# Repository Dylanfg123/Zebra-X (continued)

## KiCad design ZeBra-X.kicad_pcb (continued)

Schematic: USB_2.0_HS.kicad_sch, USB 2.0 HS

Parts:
C900, C901, C902, C903, C904: 100n; C_0402_1005Metric; Manufacturer PN CC0402KRX5R8BB104; LCSC PN C106256
C905, C906, C907, C908: 4u7; C_0402_1005Metric; Manufacturer PN CL05A475MP5NRNC; LCSC PN C23733
D900, D901, D902: CG0402MLU-3.3G; D_0402_1005Metric; Manufacturer PN CG0402MLU-3.3G; LCSC PN C2655393
D903: PMEG1030EJ,115; D_SOD-323F; Manufacturer PN PMEG1030EJ,115; LCSC PN C133633
FB900: 120R; L_0402_1005Metric; Manufacturer PN BLM15PX121SN1D; LCSC PN C88970
J900: GMSB0522132EU; Manufacturer PN GMSB0522132EU
R900: 1K; R_0402_1005Metric; Manufacturer PN RC0402FR-071KL; LCSC PN C106235
R901: 22R; R_0402_1005Metric; Manufacturer PN RC0402FR-0722RL; LCSC PN C114765
R902: 8K06; R_0402_1005Metric; Manufacturer PN RC0402FR-078K06L; LCSC PN C276278
R903: 12K; R_0402_1005Metric; Manufacturer PN RTT021202FTH; LCSC PN C102781
R904: 4K7; R_0402_1005Metric; Manufacturer PN RC0402FR-074K7L; LCSC PN C105871
U900: USB3320C-EZK; QFN32_5X5MC_MCH; Manufacturer PN USB3320C-EZK; LCSC PN C52447
U901: TPS2051CDBV; SOT-23-5; Manufacturer PN TPS2051CDBVR; LCSC PN C129581
X900: ECS-2520MV-130-BN-TR; Oscillator_SMD_ECS_2520MV-xxx-xx-4Pin_2.5x2.0mm; Manufacturer PN ECS-2520MV-130-BN-TR

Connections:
+1V8: C900.1, C902.1, C903.1, C904.1, R900.2, U900.14 (REFSEL2), U900.28 (VDD18), U900.30 (VDD18), U900.32 (VDDIO), X900.1 (EN), X900.4 (VDD); also elsewhere on the board
+3V3: C901.1, U900.20 (VDD33), U900.21 (VBAT); also elsewhere on the board
+5V: C907.1, U901.5 (IN); also elsewhere on the board
+5V_USB_SW: C908.1, D903.2 (A), U901.1 (OUT)
/[9] USB 2.0 HS/CLK_13MHZ: R901.1, X900.3 (OUT)
/[9] USB 2.0 HS/USB_HS_D_N: D900.1 (K), J900.2 (D-), U900.19 (DM)
/[9] USB 2.0 HS/USB_HS_D_P: D901.1 (K), J900.3 (D+), U900.18 (DP)
/[9] USB 2.0 HS/USB_HS_ID: D902.1 (K), J900.4 (ID), U900.23 (ID)
/[9] USB 2.0 HS/USB_HS_VBUS_FILT: C905.1, D903.1 (K), FB900.1, R903.2
/[9] USB 2.0 HS/USB_PHY_CPEN: R904.1, U900.17 (CPEN), U901.4 (EN)
/[9] USB 2.0 HS/USB_PHY_RBIAS: R902.1, U900.24 (RBIAS)
/[9] USB 2.0 HS/USB_PHY_VBUS: R903.1, U900.22 (VBUS)
/[9] USB 2.0 HS/USB_REFCLK_13MHZ: R901.2, U900.26 (REFCLK)
GND: C900.2, C901.2, C902.2, C903.2, C904.2, C905.2, C906.2, C907.2, C908.2, D900.2 (A), D901.2 (A), D902.2 (A), J900.5 (GND), R902.2, R904.2, U900.8 (REFSEL0), U900.11 (REFSEL1), U900.33 (GND), U901.2 (GND), X900.2 (GND); also elsewhere on the board
GNDPWR: J900.SH; also elsewhere on the board
unnamed: C906.1, FB900.2, J900.1 (VBUS)
USB_CLK: U900.1 (CLKOUT); also elsewhere on the board
USB_DATA0: U900.3 (DATA0); also elsewhere on the board
USB_DATA1: U900.4 (DATA1); also elsewhere on the board
USB_DATA2: U900.5 (DATA2); also elsewhere on the board
USB_DATA3: U900.6 (DATA3); also elsewhere on the board
USB_DATA4: U900.7 (DATA4); also elsewhere on the board
USB_DATA5: U900.9 (DATA5); also elsewhere on the board
USB_DATA6: U900.10 (DATA6); also elsewhere on the board
USB_DATA7: U900.13 (DATA7); also elsewhere on the board
USB_DIR: U900.31 (DIR); also elsewhere on the board
USB_NRST: R900.1, U900.27 (RESETB); also elsewhere on the board
USB_NXT: U900.2 (NXT); also elsewhere on the board
USB_STP: U900.29 (STP); also elsewhere on the board

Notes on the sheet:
USB PHY Reference Clock (13MHz)
ULPI
[9] USB 2.0 High-Speed (OTG)
REFSEL[2:0]=100 -> REFCLK=13MHz
USB HS PHY & Mini AB Connector

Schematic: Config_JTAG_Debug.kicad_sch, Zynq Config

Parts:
C300, C304, C306, C307, C308, C309, C310, C311, C312, C313, C314, C316, C318: 100n; C_0402_1005Metric; Manufacturer PN CC0402KRX5R8BB104; LCSC PN C106256
C301, C302, C303, C305, C315: 4u7; C_0402_1005Metric; Manufacturer PN CL05A475MP5NRNC; LCSC PN C23733
D300, D308, D309: LED_GREEN; LED_0402_1005Metric; Manufacturer PN SZYY0402YG; LCSC PN C434449
D301, D302, D303, D304, D306, D307: CG0402MLU-3.3G; D_0402_1005Metric; Manufacturer PN CG0402MLU-3.3G; LCSC PN C2655393
D305: PMEG1030EJ,115; D_SOD-323F; Manufacturer PN PMEG1030EJ,115; LCSC PN C133633
FB300, FB301, FB302: 120R; L_0402_1005Metric; Manufacturer PN BLM15PX121SN1D; LCSC PN C88970
J300: DigilentH2SHeader; PinHeader_1x06_P2.54mm_Vertical
J301: USB3100-30-A; CONN_USB3100-30-A_GCT; Manufacturer PN USB3100-30-A
Q300: T2N7002AK,LM; SOT23_TOS; Manufacturer PN T2N7002AK,LM; LCSC PN C516175
R300, R301, R302, R303, R304: 4K7; R_0402_1005Metric; Manufacturer PN RC0402FR-074K7L; LCSC PN C105871
R305, R306, R307, R308, R329, R330, R331, R332, R333, R334, R335, R338: 22R; R_0402_1005Metric; Manufacturer PN RC0402FR-0722RL; LCSC PN C114765
R309, R336, R337: 510R; R_0402_1005Metric; Manufacturer PN RC0402FR-07510RL; LCSC PN C276273
R310, R312, R314, R316, R319: 20K; R_0402_1005Metric; Manufacturer PN RC0402FR-0720KL; LCSC PN C93942
R311, R313, R315, R318, R321: 1K; R_0402_1005Metric; Manufacturer PN RC0402FR-071KL; LCSC PN C106235
R317, R320: DNP_0R; R_0402_1005Metric; not fitted
R322, R323: 100K; R_0402_1005Metric; Manufacturer PN RC0402FR-07100KL; LCSC PN C60491
R324, R326, R327, R328: 12K; R_0402_1005Metric; Manufacturer PN RTT021202FTH; LCSC PN C102781
R325: 2K49; R_0402_1005Metric; Manufacturer PN RC0402FR-072K49L; LCSC PN C145071
SW300: SKRPANE010; SW_Push_1P1T_NO_Vertical_Wuerth_434133025816; Manufacturer PN SKRPANE010; LCSC PN C470426
SW301: 219-3LPST; SW_DIP_SPSTx03_Slide_6.7x9.18mm_W8.61mm_P2.54mm_LowProfile; Manufacturer PN 219-3LPST
U200: XC7Z010-2CLG400I; CLG400_XIL; Manufacturer PN XC7Z010-2CLG400I; LCSC PN C2840993
U300: FT2232HL; LQFP-64_10x10mm_P0.5mm; Manufacturer PN FT2232HL-REEL; LCSC PN C27882
U301: 93LC65B-I/SN; SOIC-8_3.9x4.9mm_P1.27mm; Manufacturer PN 93LC56B-I/SN; LCSC PN C183620
X300: ECS-2520MV-120-BN; Oscillator_SMD_ECS_2520MV-xxx-xx-4Pin_2.5x2.0mm; Manufacturer PN ECS-2520MV-120-BN-TR; LCSC PN C405460

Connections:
+3V3: C300.1, C310.1, C311.1, C312.1, C313.1, C314.1, C316.1, C318.1, FB301.1, FB302.1, J300.6 (VDD), R300.1, R301.1, R302.1, R303.1, R304.1, R309.2, R317.2, R320.2, R324.2, R326.2, R327.2, R336.2, R337.2, SW301.4, SW301.5, SW301.6, U200.M6 (CFGBVS_0), U300.20 (VCCIO), U300.31 (VCCIO), U300.42 (VCCIO), U300.50 (VREGIN), U300.56 (VCCIO), U301.8 (VCC), X300.1 (Tri-State), X300.4 (VDD); also elsewhere on the board
/[3] Config, JTAG, Debug/+1V8_FTDI: C307.1, C308.1, C309.1, C315.1, U300.12 (VCORE), U300.37 (VCORE), U300.49 (VREGOUT), U300.64 (VCORE)
/[3] Config, JTAG, Debug/+5V_USB_B: C301.1, FB300.1, J301.1 (VBUS)
/[3] Config, JTAG, Debug/CLK_12MHZ: R338.1, X300.3 (OUT)
/[3] Config, JTAG, Debug/FTDI_EECLK: R326.1, U300.62 (EECLK), U301.2 (SCLK)
/[3] Config, JTAG, Debug/FTDI_EECS: R327.1, U300.63 (EECS), U301.1 (CS)
/[3] Config, JTAG, Debug/FTDI_EEDAT: R325.1, U300.61 (EEDATA), U301.3 (DI)
/[3] Config, JTAG, Debug/FTDI_NPOR: R333.1, U300.22 (ADBUS5)
/[3] Config, JTAG, Debug/FTDI_OSCI: R338.2, U300.2 (OSCI)
/[3] Config, JTAG, Debug/FTDI_REF: R328.2, U300.6 (REF)
/[3] Config, JTAG, Debug/FTDI_RX: R335.1, U300.39 (BDBUS1)
/[3] Config, JTAG, Debug/FTDI_RX_LED_A: D308.2 (A), R336.1
/[3] Config, JTAG, Debug/FTDI_RX_LED_K: D308.1 (K), U300.54 (BCBUS3)
/[3] Config, JTAG, Debug/FTDI_TCK: R329.1, U300.16 (ADBUS0)
/[3] Config, JTAG, Debug/FTDI_TDI: R330.1, U300.17 (ADBUS1)
/[3] Config, JTAG, Debug/FTDI_TDO: R331.1, U300.18 (ADBUS2)
/[3] Config, JTAG, Debug/FTDI_TMS: R332.1, U300.19 (ADBUS3)
/[3] Config, JTAG, Debug/FTDI_TX: R334.1, U300.38 (BDBUS0)
/[3] Config, JTAG, Debug/FTDI_TX_LED_A: D309.2 (A), R337.1
/[3] Config, JTAG, Debug/FTDI_TX_LED_K: D309.1 (K), U300.55 (BCBUS4)
/[3] Config, JTAG, Debug/FTDI_VPLL: C303.1, C304.1, FB301.2, U300.9 (VPLL)
/[3] Config, JTAG, Debug/JTAG_TCK: D303.1 (K), J300.4 (TCK), R307.2
/[3] Config, JTAG, Debug/JTAG_TDI: D301.1 (K), J300.2 (TDI), R305.2
/[3] Config, JTAG, Debug/JTAG_TDO: D302.1 (K), J300.3 (TDO), R306.2
/[3] Config, JTAG, Debug/JTAG_TMS: D304.1 (K), J300.1 (TMS), R308.2
/[3] Config, JTAG, Debug/LED_DONE_A: D300.2 (A), R309.1
/[3] Config, JTAG, Debug/LED_DONE_K: D300.1 (K), Q300.3 (D)
/[3] Config, JTAG, Debug/M0: R310.1, R311.2, SW301.1
/[3] Config, JTAG, Debug/M1: R312.1, R313.2, SW301.2
/[3] Config, JTAG, Debug/M2: R314.1, R315.2, SW301.3
/[3] Config, JTAG, Debug/M3: R316.1, R317.1, R318.2
/[3] Config, JTAG, Debug/M4: R319.1, R320.1, R321.2
/[3] Config, JTAG, Debug/NINIT: R303.2, U200.R10 (INIT_B_0)
/[3] Config, JTAG, Debug/NPROGRAM: R304.2, SW300.1, U200.L6 (PROGRAM_B_0)
/[3] Config, JTAG, Debug/TCK: R307.1, R329.2, U200.F9 (TCK_0)
/[3] Config, JTAG, Debug/TDI: R300.2, R305.1, R330.2, U200.G6 (TDI_0)
/[3] Config, JTAG, Debug/TDO: R306.1, R331.2, U200.F6 (TDO_0)
/[3] Config, JTAG, Debug/TMS: R301.2, R308.1, R332.2, U200.J6 (TMS_0)
/[3] Config, JTAG, Debug/USB_FTDI_D+: D307.1 (K), J301.3 (D+), U300.8 (DP)
/[3] Config, JTAG, Debug/USB_FTDI_D-: D306.1 (K), J301.2 (D-), U300.7 (DM)
/[3] Config, JTAG, Debug/VUSB_FILT: C302.1, D305.2 (A), FB300.2, R322.1
DONE: Q300.1 (G), R302.2, U200.R11 (DONE_0); also elsewhere on the board
FLASH_CLK_M4: R319.2
GND: C300.2, C301.2, C302.2, C303.2, C304.2, C305.2, C306.2, C307.2, C308.2, C309.2, C310.2, C311.2, C312.2, C313.2, C314.2, C315.2, C316.2, C318.2, D301.2 (A), D302.2 (A), D303.2 (A), D304.2 (A), D306.2 (A), D307.2 (A), J300.5 (GND), J301.5 (GND), Q300.2 (S), R311.1, R313.1, R315.1, R318.1, R321.1, R323.2, R328.1, SW300.2, U200.K9 (VP_0), U200.K10 (VREFN_0), U200.L9 (VREFP_0), U200.L10 (VN_0), U200.M9 (DXP_0), U200.M10 (DXN_0), U300.1 (GND), U300.5 (GND), U300.10 (AGND), U300.11 (GND), U300.13 (TEST), U300.15 (GND), U300.25 (GND), U300.35 (GND), U300.47 (GND), U300.51 (GND), U301.5 (GND), X300.2 (GND); also elsewhere on the board
GNDPWR: J301.6 (Shield); also elsewhere on the board
unnamed: C305.1, C306.1, FB302.2, U300.4 (VPHY)
unnamed: R322.2, R323.1, U300.14 (~RESET)
unnamed: R324.1, R325.2, U301.4 (DO)
PS_NPOR: R333.2; also elsewhere on the board
QSPI_DQ0_M3: R316.2; also elsewhere on the board
QSPI_DQ1_M1: R312.2; also elsewhere on the board
QSPI_DQ2_M2: R314.2; also elsewhere on the board
QSPI_DQ3_M0: R310.2; also elsewhere on the board
UART1_RX: R334.2; also elsewhere on the board
UART1_TX_VCFG1: R335.2; also elsewhere on the board
VCC: D305.1 (K); also elsewhere on the board

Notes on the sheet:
CFGBVS=1 -> VCC0=3V3 VP=VN=GND -> Not Used VREFP=VREFN=GND -> On-chip ref
M4 -> PLL Bypass
M3 -> JTAG Cascade/Independent Mode
[2] Zynq Config, JTAG, Debug
M[0 2 1]=Boot Mode
Boot Mode MIO Strapping Pins (Zynq TRM p167)
Zynq Config, JTAG
FTDI JTAG Programmer and USB-to-UART

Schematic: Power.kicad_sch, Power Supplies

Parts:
C100, C103, C104, C107, C108, C109, C112, C113, C114, C117, C118, C119, C122, C123, C124, C127: 22u; C_1210_3225Metric; Manufacturer PN CL32A226MOJNNNE; LCSC PN C100086
C101, C102, C105, C110, C115, C120: 100n; C_0402_1005Metric; Manufacturer PN CC0402KRX5R8BB104; LCSC PN C106256
C106, C111, C116, C121: 22p; C_0402_1005Metric; Manufacturer PN GCM1555C1H220JA16D; LCSC PN C126502
C125, C126, C128, C129: 4u7; C_0402_1005Metric; Manufacturer PN CL05A475MP5NRNC; LCSC PN C23733
C130: 1n; C_1206_3216Metric; Manufacturer PN 202R18W102KV4E; LCSC PN C173242
D100: PMEG1030EJ,115; D_SOD-323F; Manufacturer PN PMEG1030EJ,115; LCSC PN C133633
D101: LED_GREEN; LED_0402_1005Metric; Manufacturer PN SZYY0402YG; LCSC PN C434449
J100: CON-SOCJ-2155; GRAVITECH_CON-SOCJ-2155; Manufacturer PN CON-SOCJ-2155
L100, L101, L102, L103: 2u2; L_Taiyo-Yuden_NR-60xx; Manufacturer PN NR6028T2R2N
Q100: T2N7002AK,LM; SOT23_TOS; Manufacturer PN T2N7002AK,LM; LCSC PN C516175
R100, R104, R107, R109, R112, R114, R117, R119, R122, R126: 100K; R_0402_1005Metric; Manufacturer PN RC0402FR-07100KL; LCSC PN C60491
R101, R103, R105, R108, R110, R113, R115, R118, R120, R124, R125: 12K; R_0402_1005Metric; Manufacturer PN RTT021202FTH; LCSC PN C102781
R102: 4K7; R_0402_1005Metric; Manufacturer PN RC0402FR-074K7L; LCSC PN C105871
R106: 68K; R_0402_1005Metric; Manufacturer PN RC0402FR-0768KL; LCSC PN C137947
R111: 200K; R_0402_1005Metric; Manufacturer PN RC0402FR-07200KL; LCSC PN C114763
R116: 124K; R_0402_1005Metric; Manufacturer PN RC0402FR-07124KL; LCSC PN C138062
R121: 435K; R_0402_1005Metric; Manufacturer PN RC0402FR-07453KL; LCSC PN C137978
R123: 510R; R_0402_1005Metric; Manufacturer PN RC0402FR-07510RL; LCSC PN C276273
R127: 1K; R_0402_1005Metric; Manufacturer PN RC0402FR-071KL; LCSC PN C106235
R128: DNP_1M; R_1206_3216Metric; not fitted
U100: LS1205EVD33; DFN-10-1EP_3x3mm_P0.5mm_EP1.55x2.48mm; Manufacturer PN LS1205EVD33
U101, U102, U103, U104: SY8003ADFC; DFN-8-1EP_2x2mm_P0.5mm_EP1.05x1.75mm; Manufacturer PN SY8003ADFC; LCSC PN C178236
U105: BD3539FVM; MSOP-8_3x3mm_P0.65mm; Manufacturer PN BD3539FVM-TR; LCSC PN C213437

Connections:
+0V675: C127.1, C128.1, U105.3 (VTTS), U105.8 (VTT); also elsewhere on the board
+0V675_REF: C129.1, U105.4 (VREF); also elsewhere on the board
+1V0: C106.1, C107.1, C108.1, L100.2, R106.1; also elsewhere on the board
+1V8: C111.1, C112.1, C113.1, L101.2, R111.1; also elsewhere on the board
+1V35: C116.1, C117.1, C118.1, L102.2, R116.1, R127.1; also elsewhere on the board
+3V3: C121.1, C122.1, C123.1, L103.2, R121.1; also elsewhere on the board
+5V: C103.1, C104.1, C109.1, C114.1, C119.1, C124.1, C126.1, R103.2, R105.1, R108.2, R113.2, R118.2, R123.2, U100.8 (OUT), U100.9 (OUT), U100.10 (OUT), U101.3 (IN), U102.3 (IN), U103.3 (IN), U104.3 (IN), U105.6 (VCC), U105.7 (VTT_IN); also elsewhere on the board
/[1] Power/DDR_VTT_EN: R125.1, R126.1, U105.2 (EN)
/[1] Power/DDR_VTT_VDDQ: C125.1, R127.2, U105.5 (VDDQ)
/[1] Power/EFUSE_ILIM: R102.1, U100.5 (ILIM)
/[1] Power/EFUSE_SS: C102.1, U100.6 (SS)
/[1] Power/EFUSE_VCP: R101.1, U100.4 (VCP)
/[1] Power/EN_1V0: R105.2, U101.7 (EN)
/[1] Power/EN_1V8: R110.2, U102.7 (EN)
/[1] Power/EN_1V35: R115.2, U103.7 (EN)
/[1] Power/EN_3V3: R120.2, U104.7 (EN)
/[1] Power/FB_1V0: C106.2, R106.2, R107.1, U101.1 (FB)
/[1] Power/FB_1V8: C111.2, R111.2, R112.1, U102.1 (FB)
/[1] Power/FB_1V35: C116.2, R116.2, R117.1, U103.1 (FB)
/[1] Power/FB_3V3: C121.2, R121.2, R122.1, U104.1 (FB)
/[1] Power/LED_PWR_A: D101.2 (A), R123.1
/[1] Power/LED_PWR_K: D101.1 (K), Q100.3 (D)
/[1] Power/PG_1V0: C105.1, R103.1, R104.1, R110.1, U101.2 (PG)
/[1] Power/PG_1V8: C110.1, R108.1, R109.1, R115.1, U102.2 (PG)
/[1] Power/PG_1V35: C115.1, R113.1, R114.1, R120.1, R125.2, U103.2 (PG)
/[1] Power/PG_3V3: C120.1, R118.1, R119.1, R124.2, U104.2 (PG)
/[1] Power/SW_1V0: L100.1, U101.6 (LX)
/[1] Power/SW_1V8: L101.1, U102.6 (LX)
/[1] Power/SW_1V35: L102.1, U103.6 (LX)
/[1] Power/SW_3V3: L103.1, U104.6 (LX)
GND: C100.2, C101.2, C102.2, C103.2, C104.2, C105.2, C107.2, C108.2, C109.2, C110.2, C112.2, C113.2, C114.2, C115.2, C117.2, C118.2, C119.2, C120.2, C122.2, C123.2, C124.2, C125.2, C126.2, C127.2, C128.2, C129.2, C130.2, J100.2, J100.3, Q100.2 (S), R102.2, R104.2, R107.2, R109.2, R112.2, R114.2, R117.2, R119.2, R122.2, R126.2, R128.2, U100.11 (GND), U101.4 (PGND), U101.8 (SGND), U101.9 (PGND), U102.4 (PGND), U102.8 (SGND), U102.9 (PGND), U103.4 (PGND), U103.8 (SGND), U103.9 (PGND), U104.4 (PGND), U104.8 (SGND), U104.9 (PGND), U105.1 (GND); also elsewhere on the board
GNDPWR: C130.1, R128.1; also elsewhere on the board
unnamed: Q100.1 (G), R124.1
PWR_EN: C101.1, R100.2, U100.7 (EN); also elsewhere on the board
VCC: C100.1, D100.1 (K), R100.1, R101.2, U100.1 (IN), U100.2 (IN), U100.3 (IN); also elsewhere on the board
VDC: D100.2 (A), J100.1

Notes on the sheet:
VCP=1 -> V(Out)=5V V(Clamp)=5.7V I(Lim) = 10.5/4.7 = 2.2A
V(Out)=0.6*(1+Rhi/Rlo)=0.6*(1+68/100)=1.008V
V(Out)=0.6*(1+Rhi/Rlo)=0.6*(1+200/100)=1.8V
V(Out)=0.6*(1+Rhi/Rlo)=0.6*(1+453/100)=3.318V
Power sequence: +1V0 -> +1V8 -> +1V35 -> +3V3
[1] Power
DDR3L VTT Regulator
Chassis GND Connection
Input Power & eFuse
Power Sequence Good LED
V(Out)=0.6*(1+Rhi/Rlo)=0.6*(1+124K/100)=1.344V
Buck Converters
250V

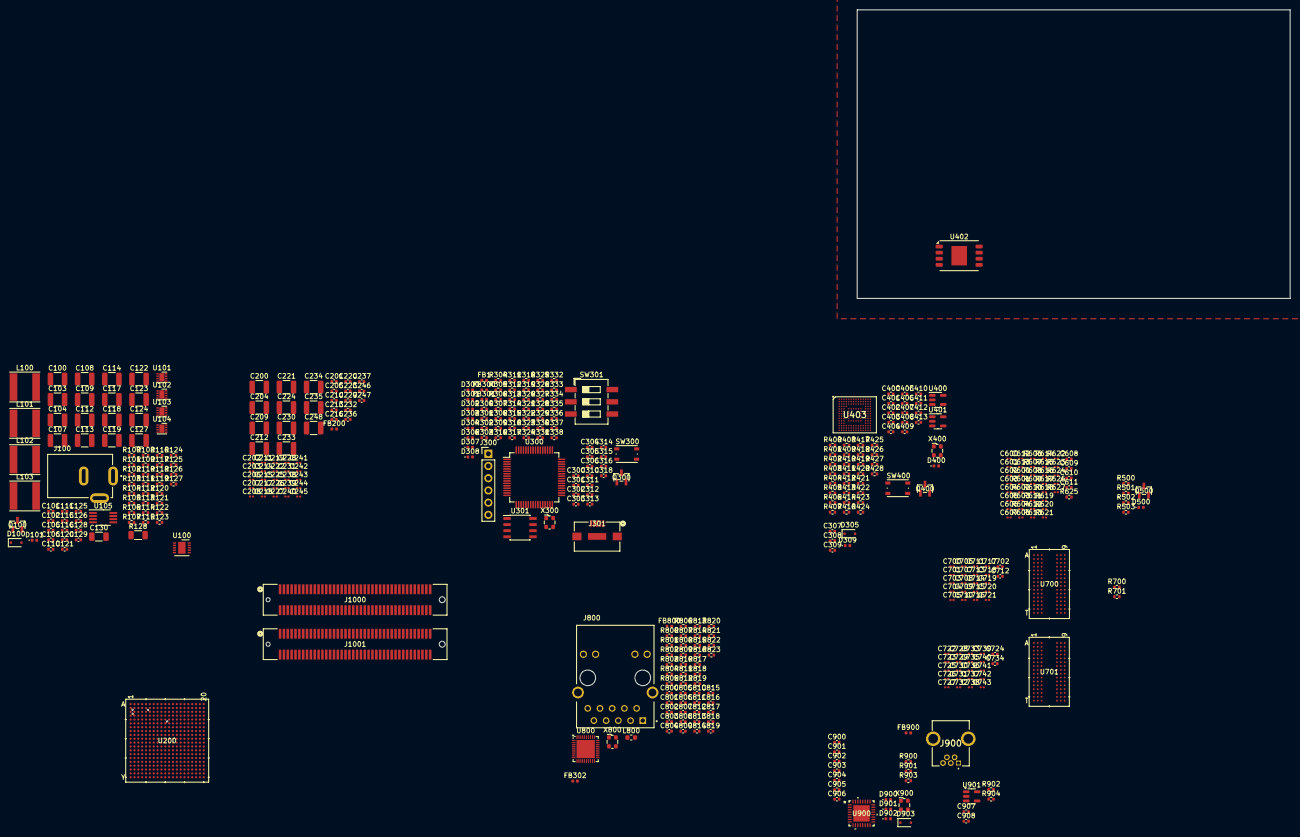
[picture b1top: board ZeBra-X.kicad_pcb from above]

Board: 10 copper layers, 90.0 x 60.0 mm, 424 parts (0 on the bottom side), 319 nets.

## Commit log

2023-12-10 Initial commit. Readme and gitignore
2023-12-10 Page 1 Power schematic done
2023-12-10 Schematic page 2 done, Zynq Power
2023-12-14 Fixed Q100 footprint
2023-12-18 Finished page 3 of schematic: Zynq Config, JTAG, Debug
2024-01-27 Finished schematic page 4: Zynq Processing System (PS), includes 128MBit QSPI flash, 33.33 MHz PS Clock, and 4Gbyte EMMC Memory
2024-01-28 Added shematic sheet 5:Zynq Programmable Logic (PL)
2024-01-28 Finished schematic page 6:Zynq DDR Interface & Termination
2024-08-24 Added page '[7] 1GB DDR3L Modules'
2024-08-24 Added placeholders for sheets 8,9, and 10
2025-01-18 Completed page 8, Gigabit Ethernet Controller
2025-01-18 started page 9, USB2.0 hub
2025-01-19 finished page 9, USB 2.0 Hub
2025-01-22 Finished first pass of schematic, needs netclass assignments and double check
